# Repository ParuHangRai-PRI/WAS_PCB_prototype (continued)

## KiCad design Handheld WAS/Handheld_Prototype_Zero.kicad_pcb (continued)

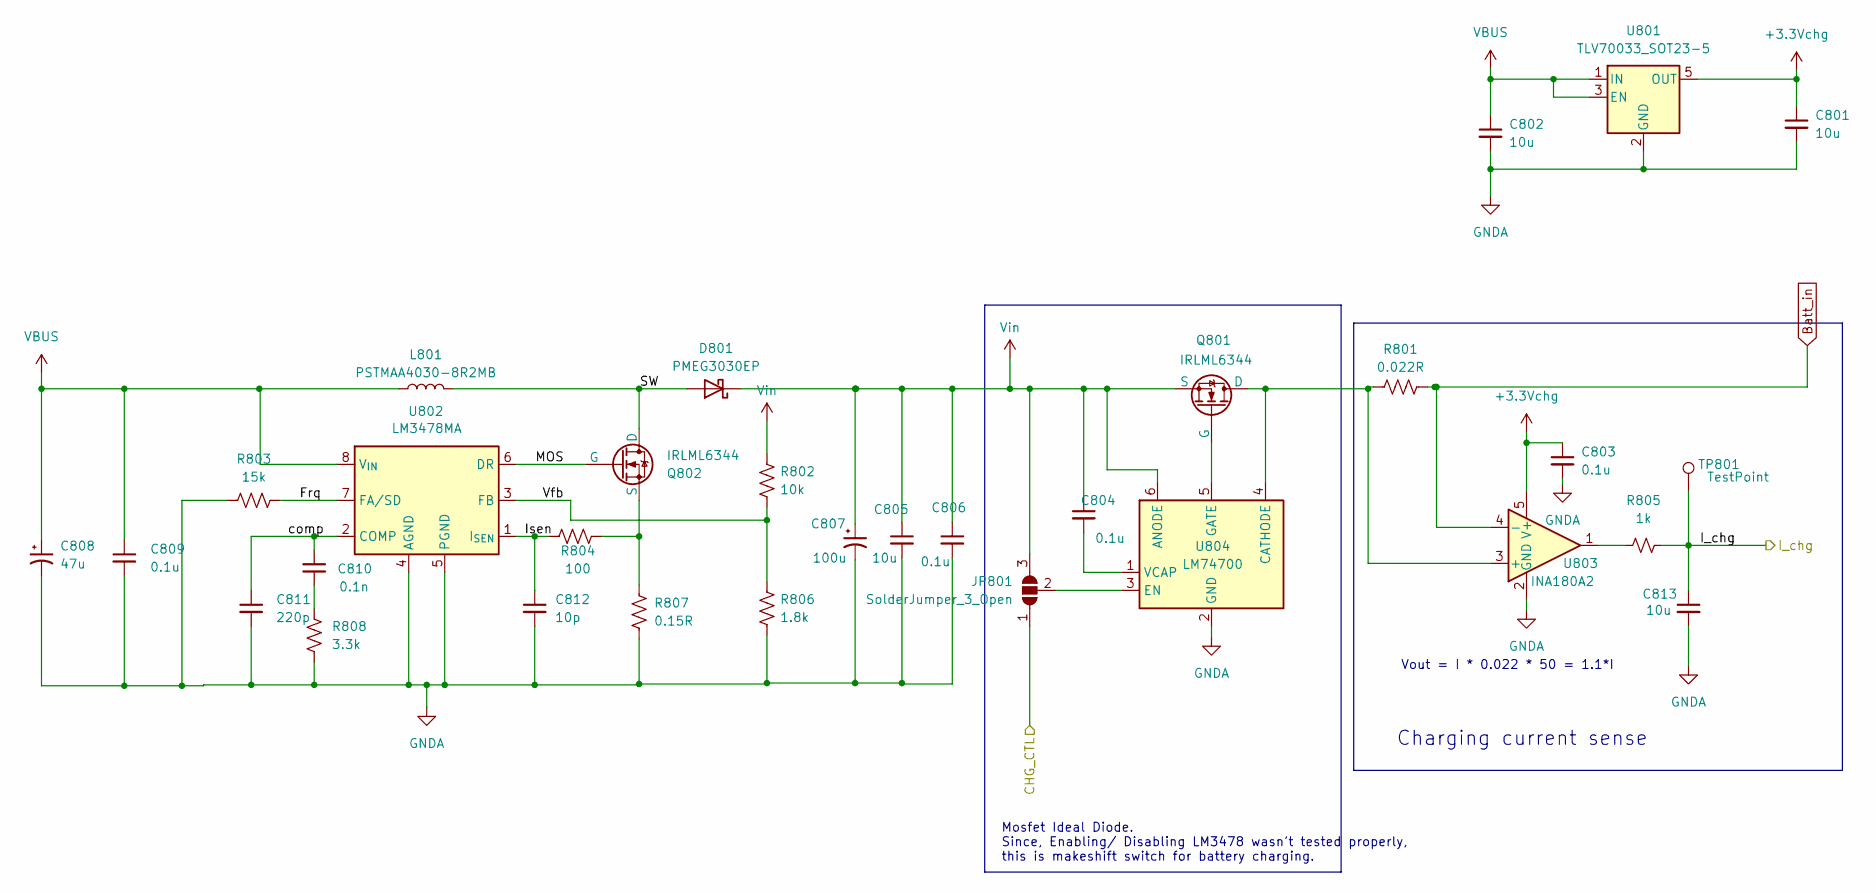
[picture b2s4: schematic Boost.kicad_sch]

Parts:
C801, C813: 10u; C_0402_1005Metric_Pad0.74x0.62mm_HandSolder; JLC Part# C315248
C802, C805: 10u; C_0603_1608Metric_Pad1.08x0.95mm_HandSolder; JLC Part# C96446
C803, C804, C806, C809: 0.1u; C_0402_1005Metric_Pad0.74x0.62mm_HandSolder; JLC Part# C1581
C807: 100u; CP_Radial_D8.0mm_P3.50mm; JLC Part# C171434
C808: 47u; CP_Elec_6.3x5.8; JLC Part# C1848745
C810: 0.1n; C_0402_1005Metric_Pad0.74x0.62mm_HandSolder; JLC Part# C1546
C811: 220p; C_0402_1005Metric_Pad0.74x0.62mm_HandSolder; JLC Part# C1530
C812: 10p; C_0402_1005Metric_Pad0.74x0.62mm_HandSolder; JLC Part# C1545
D801: PMEG3030EP; D_SOD-128; JLC Part# C255587
JP801: SolderJumper_3_Open; SolderJumper-3_P1.3mm_Open_RoundedPad1.0x1.5mm
L801: PSTMAA4030-8R2MB; IND_PSTMAA4030-8R2MB; JLC Part# C45385251
Q801, Q802: IRLML6344; SOT-23; JLC Part# C6285738
R801: 0.022R; R_1206_3216Metric_Pad1.30x1.75mm_HandSolder; JLC Part# C2941127
R802: 10k; R_0402_1005Metric_Pad0.72x0.64mm_HandSolder; JLC Part# C850723
R803: 15k; R_0402_1005Metric_Pad0.72x0.64mm_HandSolder; JLC Part# C25756
R804: 100; R_0402_1005Metric_Pad0.72x0.64mm_HandSolder; JLC Part# C850722
R805: 1k; R_0402_1005Metric_Pad0.72x0.64mm_HandSolder; JLC Part# C851849
R806: 1.8k; R_0402_1005Metric_Pad0.72x0.64mm_HandSolder; JLC Part# C25871
R807: 0.15R; R_2512_6332Metric_Pad1.40x3.35mm_HandSolder; JLC Part# C46961761
R808: 3.3k; R_0402_1005Metric_Pad0.72x0.64mm_HandSolder; JLC Part# C25890
TP801: TestPoint; TestPoint_Pad_D1.5mm
U801: TLV70033_SOT23-5; SOT-23-5; JLC Part# C11337
U802: LM3478MA; SOIC-8_3.9x4.9mm_P1.27mm; JLC Part# C115907
U803: INA180A2; SOT-23-5_HandSoldering; JLC Part# C2059691
U804: LM74700; SOT-23-6_Handsoldering; JLC Part# C2941042

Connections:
+3.3Vchg: C801.1, C803.1, U801.5 (OUT), U803.5 (V+)
/Boost_ckt/CHG_CTL: JP801.1 (A); also elsewhere on the board
/Boost_ckt/Frq: R803.1, U802.7 (FA/SD)
/Boost_ckt/I_chg: C813.1, R805.2, TP801.1; also elsewhere on the board
/Boost_ckt/Isen: C812.1, R804.1, U802.1 (I_{SEN})
/Boost_ckt/MOS: Q802.1 (G), U802.6 (DR)
/Boost_ckt/SW: D801.2 (A), L801.2, Q802.3 (D)
/Boost_ckt/Vfb: R802.1, R806.2, U802.3 (FB)
/Boost_ckt/comp: C810.1, C811.1, U802.2 (COMP)
Batt_in: R801.2, U803.4 (-); also elsewhere on the board
GNDA: C801.2, C802.2, C803.2, C805.2, C806.2, C807.2, C808.2, C809.2, C811.2, C812.2, C813.2, R803.2, R806.1, R807.2, R808.2, U801.2 (GND), U802.4 (AGND), U802.5 (PGND), U803.2 (GND), U804.2 (GND); also elsewhere on the board
unnamed: C810.2, R808.1
unnamed: JP801.2 (C), U804.3 (EN)
unnamed: Q801.3 (D), R801.1, U803.3 (+), U804.4 (CATHODE)
unnamed: Q801.1 (G), U804.5 (GATE)
unnamed: Q802.2 (S), R804.2, R807.1
unnamed: R805.1, U803.1
unnamed: C804.2, U804.1 (VCAP)
VBUS: C802.1, C808.1, C809.1, L801.1, U801.1 (IN), U801.3 (EN), U802.8 (V_{IN}); also elsewhere on the board
Vin: C804.1, C805.1, C806.1, C807.1, D801.1 (K), JP801.3 (B), Q801.2 (S), R802.2, U804.6 (ANODE)

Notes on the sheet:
Charging current sense
Vout = I * 0.022 * 50 = 1.1*I
Mosfet Ideal Diode. Since, Enabling/ Disabling LM3478 wasn't tested properly, this is makeshift switch for battery charging.

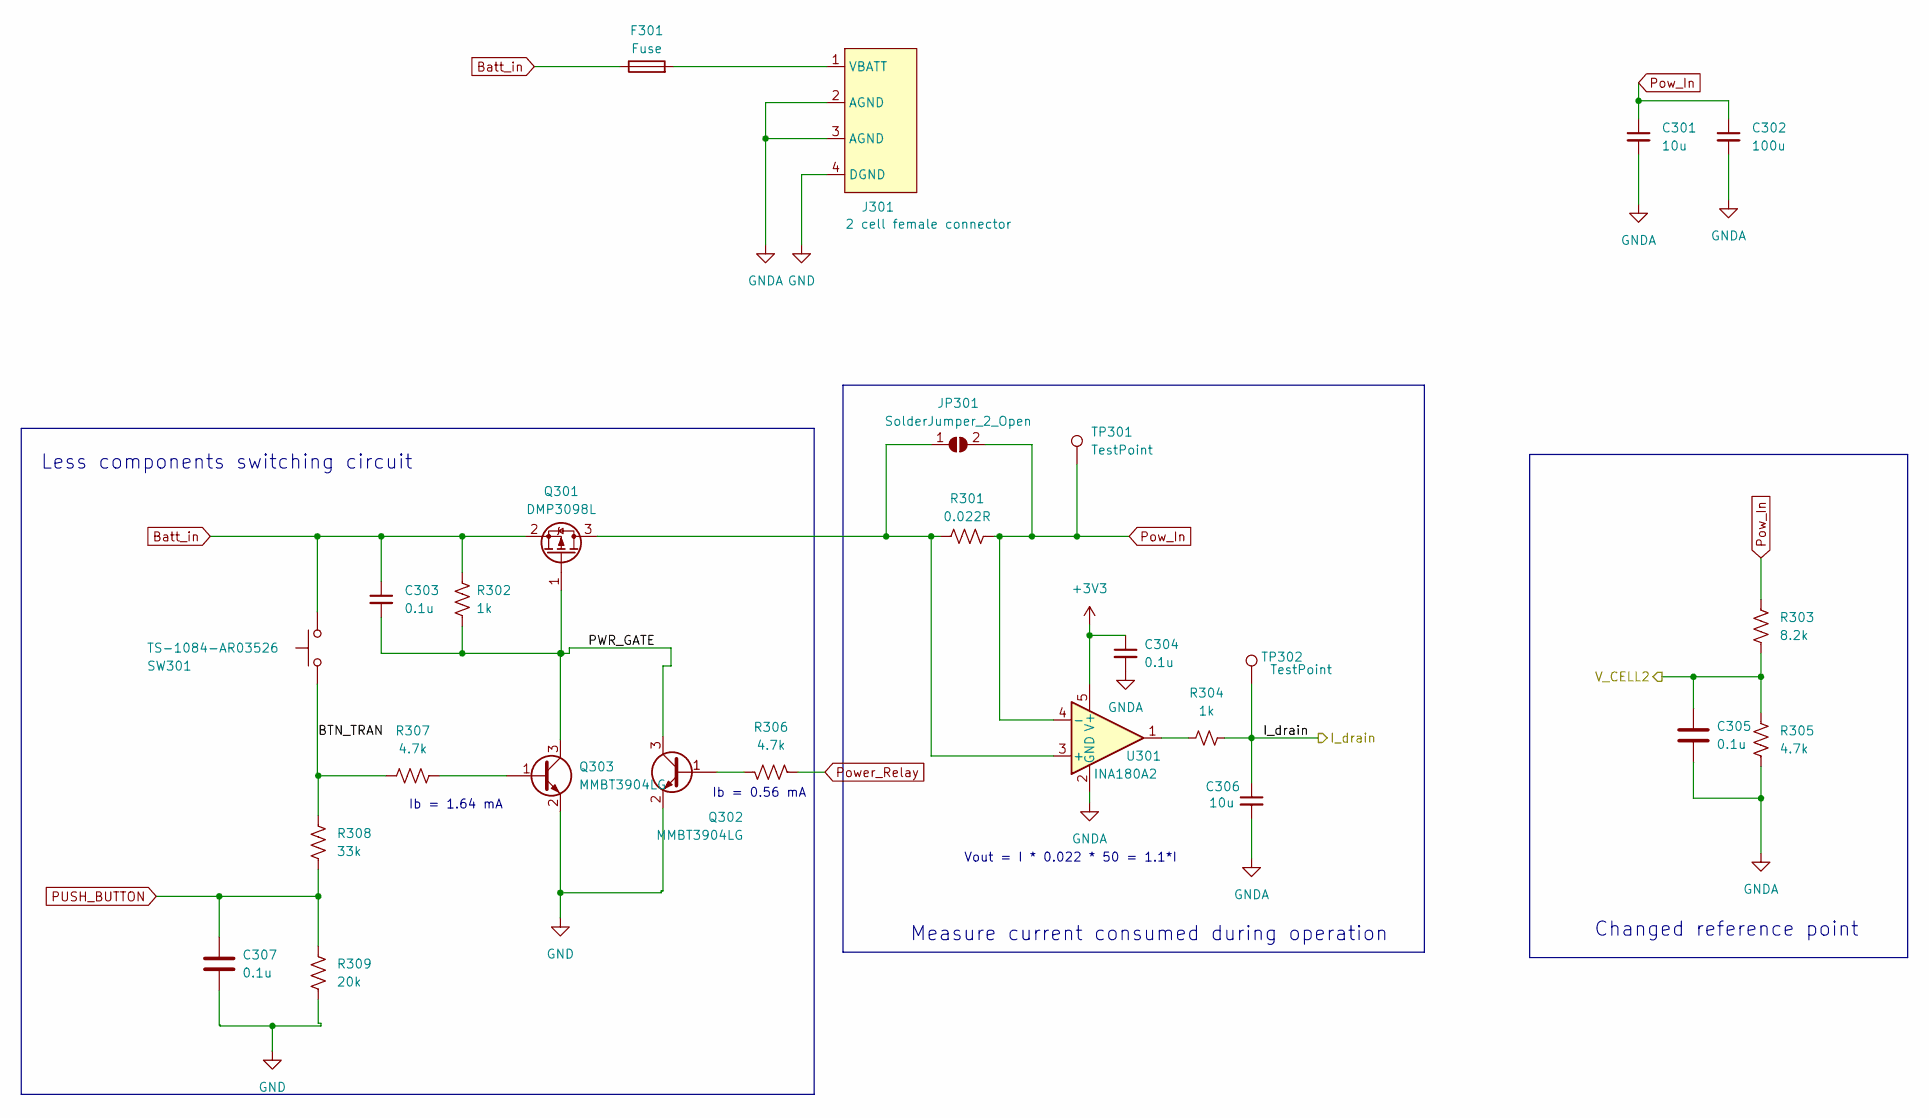
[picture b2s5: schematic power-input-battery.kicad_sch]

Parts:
C301: 10u; C_0603_1608Metric_Pad1.08x0.95mm_HandSolder; JLC Part# C96446
C302: 100u; C_1210_3225Metric_Pad1.33x2.70mm_HandSolder; JLC Part# C5372270
C303, C304, C305, C307: 0.1u; C_0402_1005Metric_Pad0.74x0.62mm_HandSolder; JLC Part# C1581
C306: 10u; C_0402_1005Metric_Pad0.74x0.62mm_HandSolder; JLC Part# C315248
F301: Fuse; Fuse_1206_3216Metric_Pad1.42x1.75mm_HandSolder; JLC Part# C207036
J301: 2 cell female connector; JST_PH_S4B-PH-SM4-TB_1x04-1MP_P2.00mm_Horizontal
JP301: SolderJumper_2_Open; SolderJumper-2_P1.3mm_Open_TrianglePad1.0x1.5mm
Q301: DMP3098L; SOT-23; JLC Part# C150492
Q302, Q303: MMBT3904LG; SOT-23; JLC Part# C94514
R301: 0.022R; R_1206_3216Metric_Pad1.30x1.75mm_HandSolder; JLC Part# C2941127
R302, R304: 1k; R_0402_1005Metric_Pad0.72x0.64mm_HandSolder; JLC Part# C851849
R303: 8.2k; R_0402_1005Metric_Pad0.72x0.64mm_HandSolder; JLC Part# C137929
R305, R306, R307: 4.7k; R_0402_1005Metric_Pad0.72x0.64mm_HandSolder; JLC Part# C105871
R308: 33k; R_0402_1005Metric_Pad0.72x0.64mm_HandSolder; JLC Part# C25779
R309: 20k; R_0402_1005Metric_Pad0.72x0.64mm_HandSolder; JLC Part# C25765
SW301: TS-1084-AR03526; SW_TS-1084-AR03526; JLC Part# C720495
TP301, TP302: TestPoint; TestPoint_Pad_D1.5mm
U301: INA180A2; SOT-23-5_HandSoldering; JLC Part# C2059691

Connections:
+3V3: C304.1, U301.5 (V+); also elsewhere on the board
/MCU/V_CELL2: C305.1, R303.1, R305.2; also elsewhere on the board
/Power Input and Battery Management/BTN_TRAN: R307.2, R308.1, SW301.2
/Power Input and Battery Management/I_drain: C306.1, R304.2, TP302.1; also elsewhere on the board
/Power Input and Battery Management/PWR_GATE: C303.2, Q301.1 (G), Q302.3 (C), Q303.3 (C), R302.2
Batt_in: C303.1, F301.1, Q301.2 (S), R302.1, SW301.1; also elsewhere on the board
GND: C307.2, J301.4 (DGND), Q302.2 (E), Q303.2 (E), R309.2; also elsewhere on the board
GNDA: C301.2, C302.2, C304.2, C305.2, C306.2, J301.2 (AGND), J301.3 (AGND), R305.1, U301.2 (GND); also elsewhere on the board
unnamed: F301.2, J301.1 (VBATT)
unnamed: JP301.1 (A), Q301.3 (D), R301.1, U301.3 (+)
unnamed: Q302.1 (B), R306.1
unnamed: Q303.1 (B), R307.1
unnamed: R304.1, U301.1
PUSH_BUTTON: C307.1, R308.2, R309.1; also elsewhere on the board
Pow_In: C301.1, C302.1, JP301.2 (B), R301.2, R303.2, TP301.1, U301.4 (-); also elsewhere on the board
Power_Relay: R306.2; also elsewhere on the board

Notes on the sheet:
Ib = 0.56 mA
Less components switching circuit
Changed reference point
Ib = 1.64 mA
Vout = I * 0.022 * 50 = 1.1*I
Measure current consumed during operation

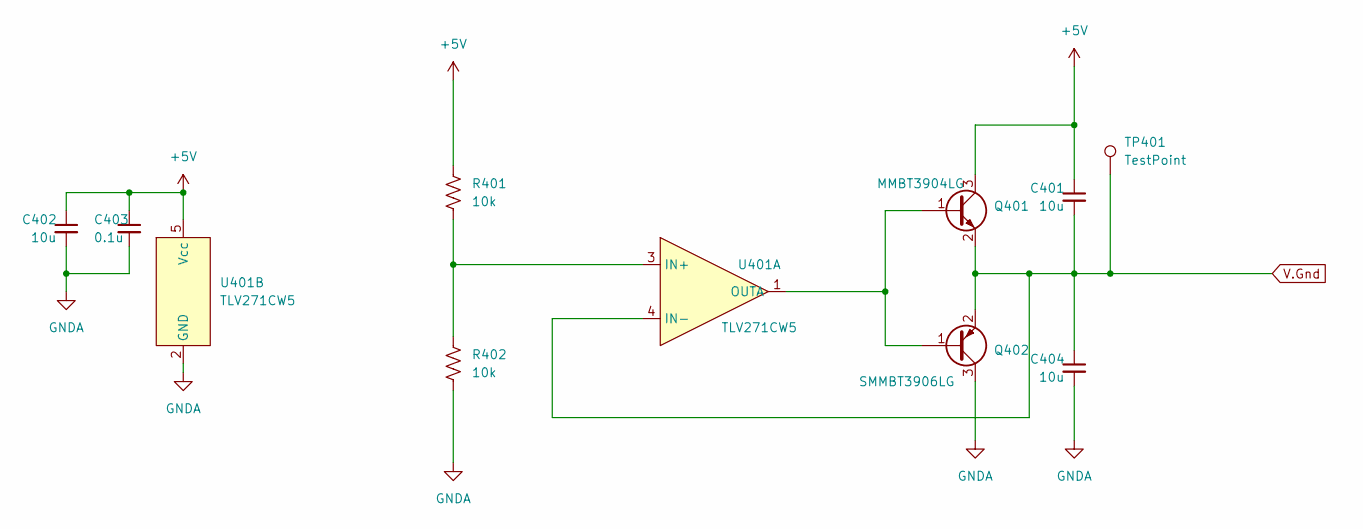
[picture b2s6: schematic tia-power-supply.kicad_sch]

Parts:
C401, C404: 10u; C_0402_1005Metric_Pad0.74x0.62mm_HandSolder; JLC Part# C315248
C402: 10u; C_0603_1608Metric_Pad1.08x0.95mm_HandSolder; JLC Part# C96446
C403: 0.1u; C_0402_1005Metric_Pad0.74x0.62mm_HandSolder; JLC Part# C1581
Q401: MMBT3904LG; SOT-23; JLC Part# C94514
Q402: SMMBT3906LG; SOT-23; JLC Part# C82762
R401, R402: 10k; R_0402_1005Metric_Pad0.72x0.64mm_HandSolder; JLC Part# C850723
TP401: TestPoint; TestPoint_Pad_D1.5mm
U401: TLV271CW5; SOT-23-5_HandSoldering; JLC Part# C150498

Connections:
+5V: C401.1, C402.1, C403.1, Q401.3 (C), R401.1, U401.5 (Vcc); also elsewhere on the board
GNDA: C402.2, C403.2, C404.2, Q402.3 (C), R402.2, U401.2 (GND); also elsewhere on the board
unnamed: Q401.1 (B), Q402.1 (B), U401.1 (OUTA)
unnamed: R401.2, R402.1, U401.3 (IN+)
V.Gnd: C401.2, C404.1, Q401.2 (E), Q402.2 (E), TP401.1, U401.4 (IN-); also elsewhere on the board

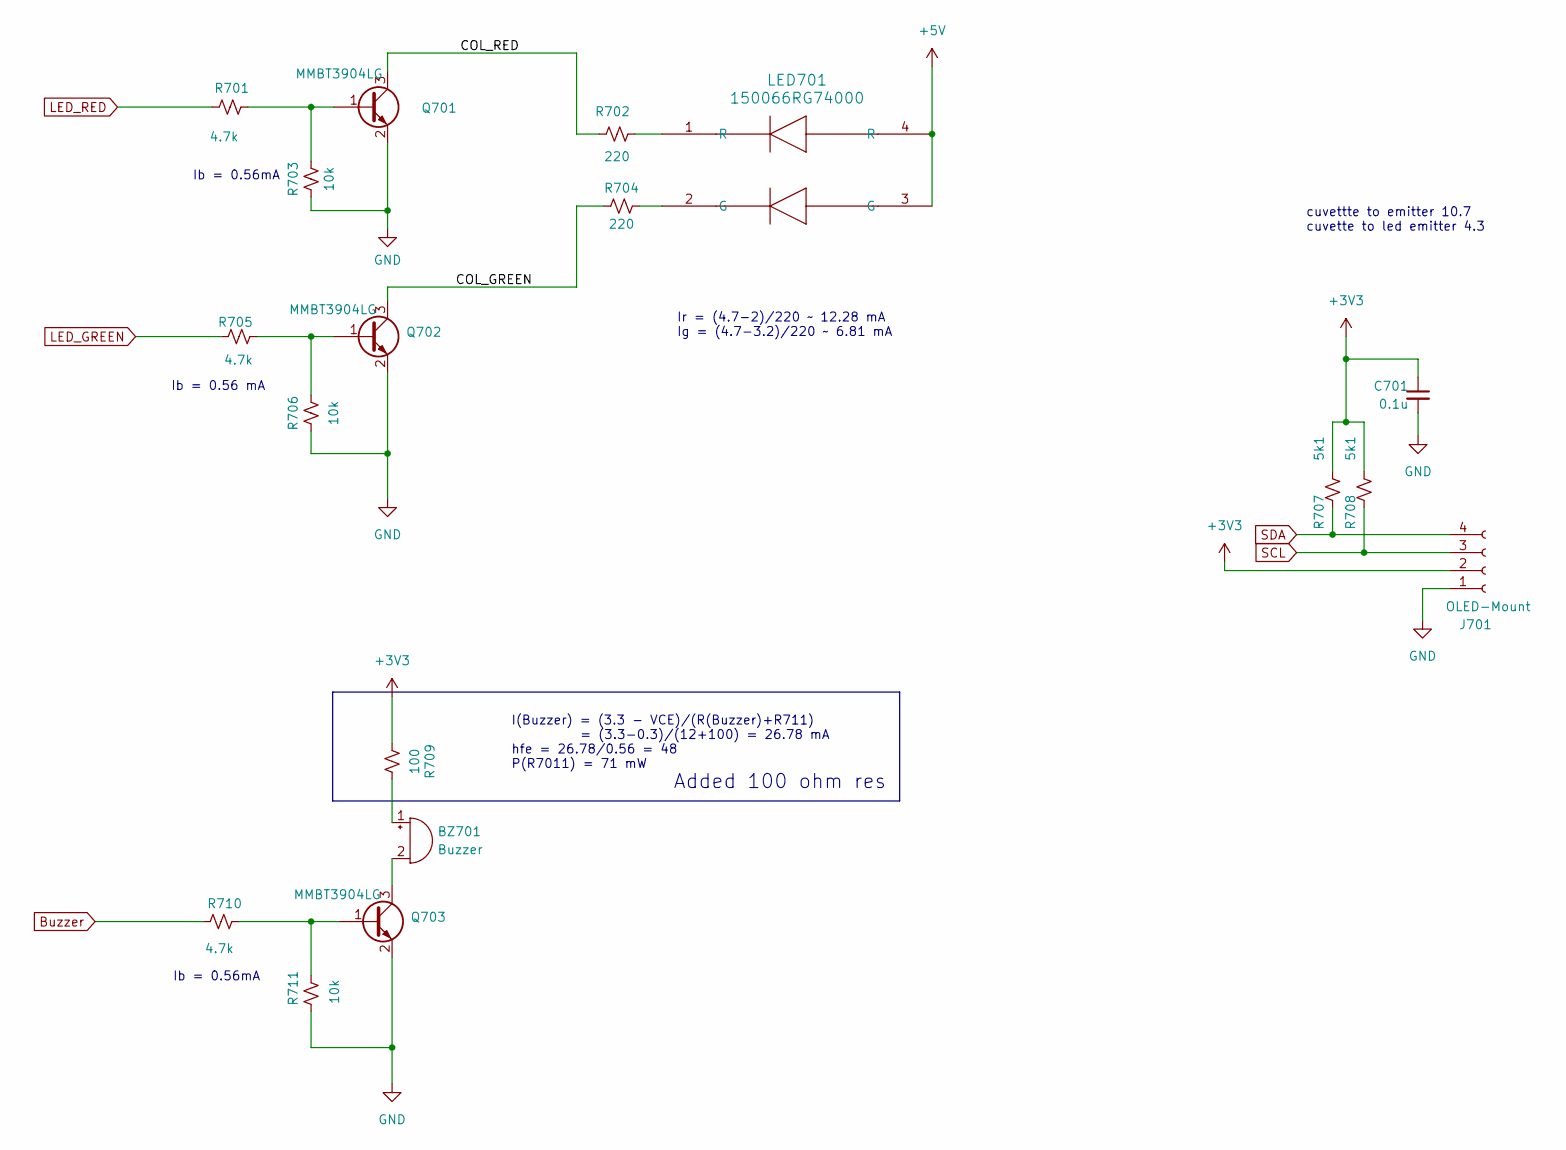
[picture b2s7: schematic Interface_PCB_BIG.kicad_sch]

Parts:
BZ701: Buzzer; BUZ_SMD_FUET-5020; JLC Part# C391029
C701: 0.1u; C_0402_1005Metric_Pad0.74x0.62mm_HandSolder; JLC Part# C1581
J701: OLED-Mount; OLED_0.96
LED701: 150066RG74000; LED_RG74000_WRE; JLC Part# C6976667
Q701, Q702, Q703: MMBT3904LG; SOT-23; JLC Part# C94514
R701, R705, R710: 4.7k; R_0402_1005Metric_Pad0.72x0.64mm_HandSolder; JLC Part# C105871
R702: 220; R_0402_1005Metric_Pad0.72x0.64mm_HandSolder; JLC Part# C38941
R703, R706, R711: 10k; R_0402_1005Metric_Pad0.72x0.64mm_HandSolder; JLC Part# C850723
R704: 220; R_0402_1005Metric_Pad0.72x0.64mm_HandSolder; JLC Part# C112291
R707, R708: 5k1; R_0402_1005Metric_Pad0.72x0.64mm_HandSolder; JLC Part# C25905
R709: 100; R_0402_1005Metric_Pad0.72x0.64mm_HandSolder; JLC Part# C850722

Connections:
+3V3: C701.1, J701.2, R707.2, R708.2, R709.2; also elsewhere on the board
+5V: LED701.3 (G), LED701.4 (R); also elsewhere on the board
/Interface/COL_GREEN: Q702.3 (C), R704.1
/Interface/COL_RED: Q701.3 (C), R702.1
Buzzer: R710.1; also elsewhere on the board
GND: C701.2, J701.1, Q701.2 (E), Q702.2 (E), Q703.2 (E), R703.1, R706.1, R711.1; also elsewhere on the board
LED_GREEN: R705.1; also elsewhere on the board
LED_RED: R701.1; also elsewhere on the board
unnamed: BZ701.2 (+), Q703.3 (C)
unnamed: BZ701.1 (-), R709.1
unnamed: LED701.2 (G), R704.2
unnamed: LED701.1 (R), R702.2
unnamed: Q701.1 (B), R701.2, R703.2
unnamed: Q702.1 (B), R705.2, R706.2
unnamed: Q703.1 (B), R710.2, R711.2
SCL: J701.3, R708.1; also elsewhere on the board
SDA: J701.4, R707.1; also elsewhere on the board

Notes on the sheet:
cuvettte to emitter 10.7 cuvette to led emitter 4.3
Ib = 0.56mA
Ir = (4.7-2)/220 ~ 12.28 mA Ig = (4.7-3.2)/220 ~ 6.81 mA
Ib = 0.56 mA
I(Buzzer) = (3.3 - VCE)/(R(Buzzer)+R711) = (3.3-0.3)/(12+100) = 26.78 mA hfe = 26.78/0.56 = 48 P(R7011) = 71 mW
Added 100 ohm res

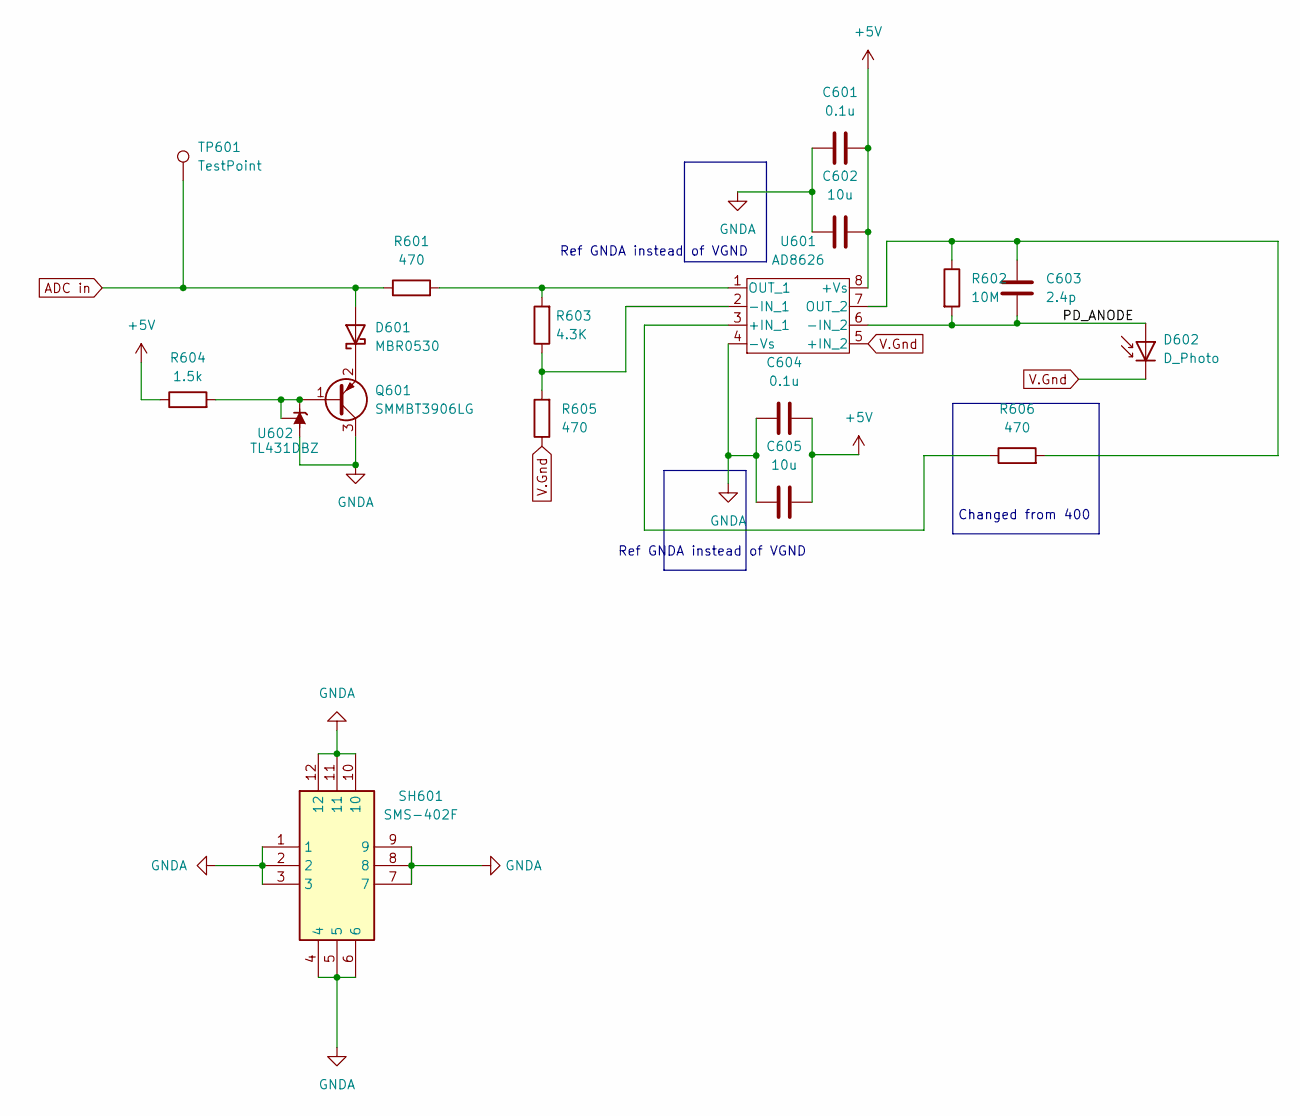
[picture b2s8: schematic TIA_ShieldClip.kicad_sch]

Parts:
C601, C604: 0.1u; C_0402_1005Metric_Pad0.74x0.62mm_HandSolder; JLC Part# C1581
C602, C605: 10u; C_0402_1005Metric_Pad0.74x0.62mm_HandSolder; JLC Part# C315248
C603: 2.4p; CAP_1111_HIQ_KNO
D601: MBR0530; D_SOD-123; JLC Part# C77336
D602: D_Photo; S1226-5BK_PCB_Solder
Q601: SMMBT3906LG; SOT-23; JLC Part# C82762
R601, R605, R606: 470; R_0402_1005Metric_Pad0.72x0.64mm_HandSolder; JLC Part# C25117
R602: 10M; R_1206_3216Metric_Pad1.30x1.75mm_HandSolder
R603: 4.3K; R_0402_1005Metric_Pad0.72x0.64mm_HandSolder; JLC Part# C477725
R604: 1.5k; R_0402_1005Metric_Pad0.72x0.64mm_HandSolder; JLC Part# C2974008
SH601: SMS-402F; SMS402F
TP601: TestPoint; TestPoint_Pad_D1.5mm
U601: AD8626; SOIC-8_3.9x4.9mm_P1.27mm; JLC Part# C653034
U602: TL431DBZ; SOT-23; JLC Part# C20628876

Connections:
+5V: C601.2, C602.2, C604.2, C605.2, R604.1, U601.8 (+Vs); also elsewhere on the board
/TiA/PD_ANODE: C603.2, D602.2 (A), R602.2, U601.6 (-IN_2)
ADC in: D601.2 (A), R601.1, TP601.1; also elsewhere on the board
GNDA: C601.1, C602.1, C604.1, C605.1, Q601.3 (C), SH601.1, SH601.2, SH601.3, SH601.4, SH601.5, SH601.6, SH601.7, SH601.8, SH601.9, SH601.10, SH601.11, SH601.12, U601.4 (-Vs), U602.3 (A); also elsewhere on the board
unnamed: D601.1 (K), Q601.2 (E)
unnamed: Q601.1 (B), R604.2, U602.1 (K), U602.2 (REF)
unnamed: R606.1, U601.3 (+IN_1)
unnamed: R603.1, R605.2, U601.2 (-IN_1)
unnamed: R601.2, R603.2, U601.1 (OUT_1)
unnamed: C603.1, R602.1, R606.2, U601.7 (OUT_2)
V.Gnd: D602.1 (K), R605.1, U601.5 (+IN_2); also elsewhere on the board

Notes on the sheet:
Ref GNDA instead of VGND
Changed from 400

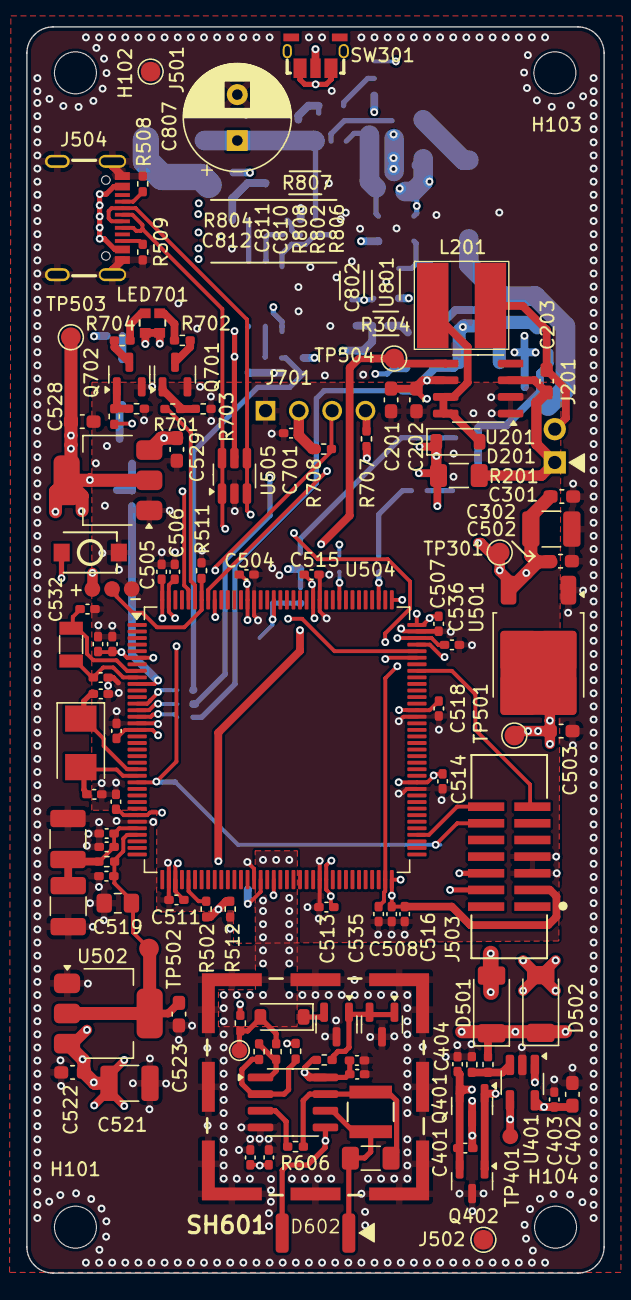
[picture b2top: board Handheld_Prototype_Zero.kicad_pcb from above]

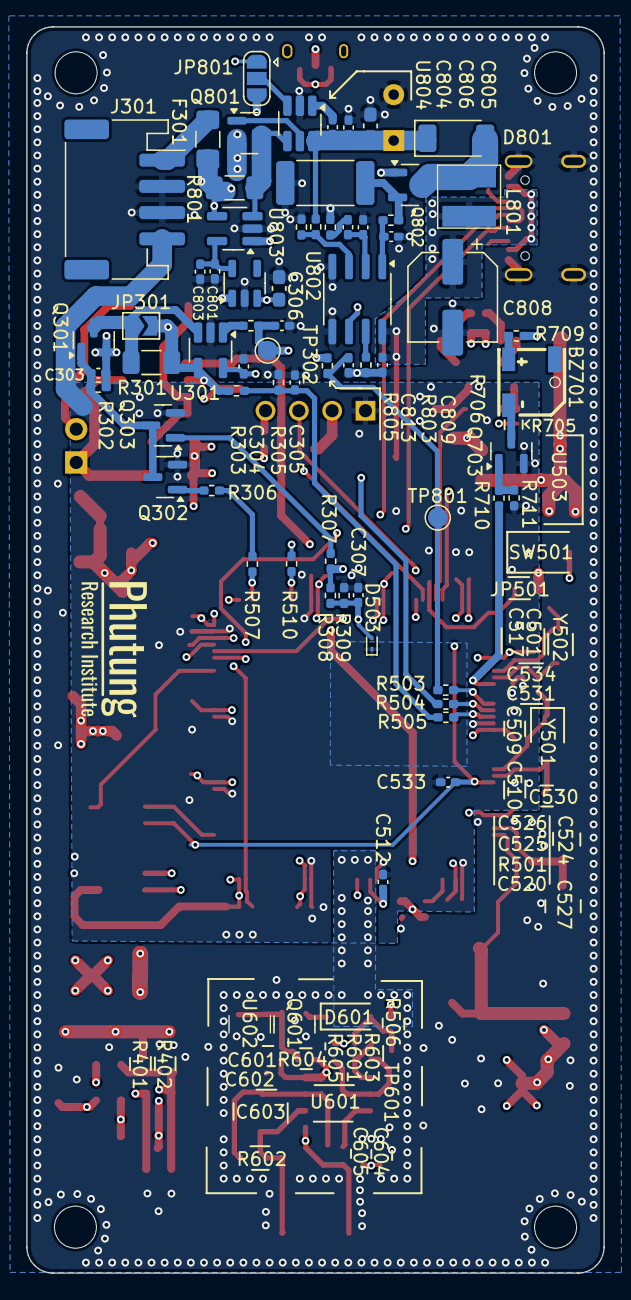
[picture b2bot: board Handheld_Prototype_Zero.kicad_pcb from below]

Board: 4 copper layers, 44.0 x 95.0 mm, 184 parts (65 on the bottom side), 90 nets.

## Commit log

2026-05-19 Added .gitignore, first commit
2026-05-19 Corrected hsitory to history in gitignore
2026-05-19 added step files to the gitignore list
2026-05-19 Uploaded handheld was and type-c project
2026-05-19 Added README.md
2026-05-19 addaed changes to CYPD3177
